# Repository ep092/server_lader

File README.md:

# server_lader

## Umbau eines ESP120 zu einem Ladegerät

### Trivia:
Das ESP120 ist ein 3kW starkes Servernetzteil mit einer Ausgangsspannung von standardmäßig 52V und bis zu >50A. Das Netzteil lässt sich allerdings leicht auf andere Spannungen umrüsten, um z.B. als Akkulader oder sehr potentes Labornetzteil eingesetzt zu werden.

### Was tut dieses Projekt?
dieses Projekt soll die zur Spannungsverstellung nötige Hilfsspannung aus den vom Netzteil zusätzlich bereitgestellten 5V erzeugen, die Ausgangsspannung regeln und für einen Ladestrom nach einem Ladeprogramm, das extern eingespeist wird, einstellen. Das Netzteil muss nur minimal gemoddet werden.

### Der Mod:
siehe elweb, eigene Bilder liegen im Unterordner "Bilder".
Einfach gesagt, werden an den beiden Pads des Potis "RV..." Kabel angelötet, die dann mit der Steuerplatine verbunden werden. Hier wird die Sollwertspannung eingespeist.

Es existieren Messwerte für 3 Sollwertspannungen:

* 61V 35,4 kOhm (-1,5V am Poti)
* 60V 42,5 kOhm (-1,3V am Poti)
* 59V 51,6 kOhm (-1,1V am Poti)

## Umbau auf eine andere Spannung für die Überspannungsabschaltung
Das Netzteil besitzt zusätzlich zur Regelspannung, die am Poti zu verändern ist, eine feste Spannung, bei der eine Überspannungsabschaltung stattfindet. Die soll das Netzteil und die angeschlossenen Verbraucher schützen. Teilweise ist es jedoch nötig, nahe an 60V zu kommen, beispielsweise, wenn man einen 48V-Bleiakkupack laden will. Daher ist in diesen Fällen die Überspannungsabschaltung auf einen leicht höheren Spannungswert zu verschieben. 

Dazu ist es notwendig einen zusätzlichen Widerstand parallel zu den bereits vorhandenen auf einer der Platinen einzulöten. Es handelt sich um einen SMD-Widerstand in Bauform 0805 mit dem Wert "473" also 47 kOhm, der direkt neben einem SMD-Bauteil im Gehäuse SOT-223-3 liegt. Im Ordner "Bilder" ist die Stelle zu sehen, wo der Widerstand eingelötet werden muss.

Wenn man über die bereits verbauten Widerstände im eingebauten Zustand misst, kommt man auf 4,096 Ohm. Mit einem parallel geschaltenen 51,6 kOhm Widerstand kommt man so auf einen Widerstand von 3,79kOhm

Es wird hier allerdings ein Widerstand mit 47 kOhm empfohlen, da mit diesem 60V gerade so erreicht werden, aber die Kondensatoren des Netzteils noch nicht beschädigt werden. Diese halten 63V aus. Für noch höhere Ausgangsspannungen müssten die Kondensatoren durch andere Typen mit 80V Festigkeit getauscht werden. Zusätzlich wird das Netzteil ab ca 61-62V instabil.

## Änderungen für Hardwareversion 2:
 
* Footprint für Stecker anpassen
* zusätzlicher Kondensator für AREF
* Micromatch-Stecker auf Display Platine auf Unterseite verlegen
* zweiter Stecker für I2C, um das OLED anzuschließen (JST XH, stehend)

## TODOs Software:

* I2C-Auswertung von Lüfter und Temperaturen
* Umbau auf so ein kleines OLED-Display z.b. mit der U8g-Lib

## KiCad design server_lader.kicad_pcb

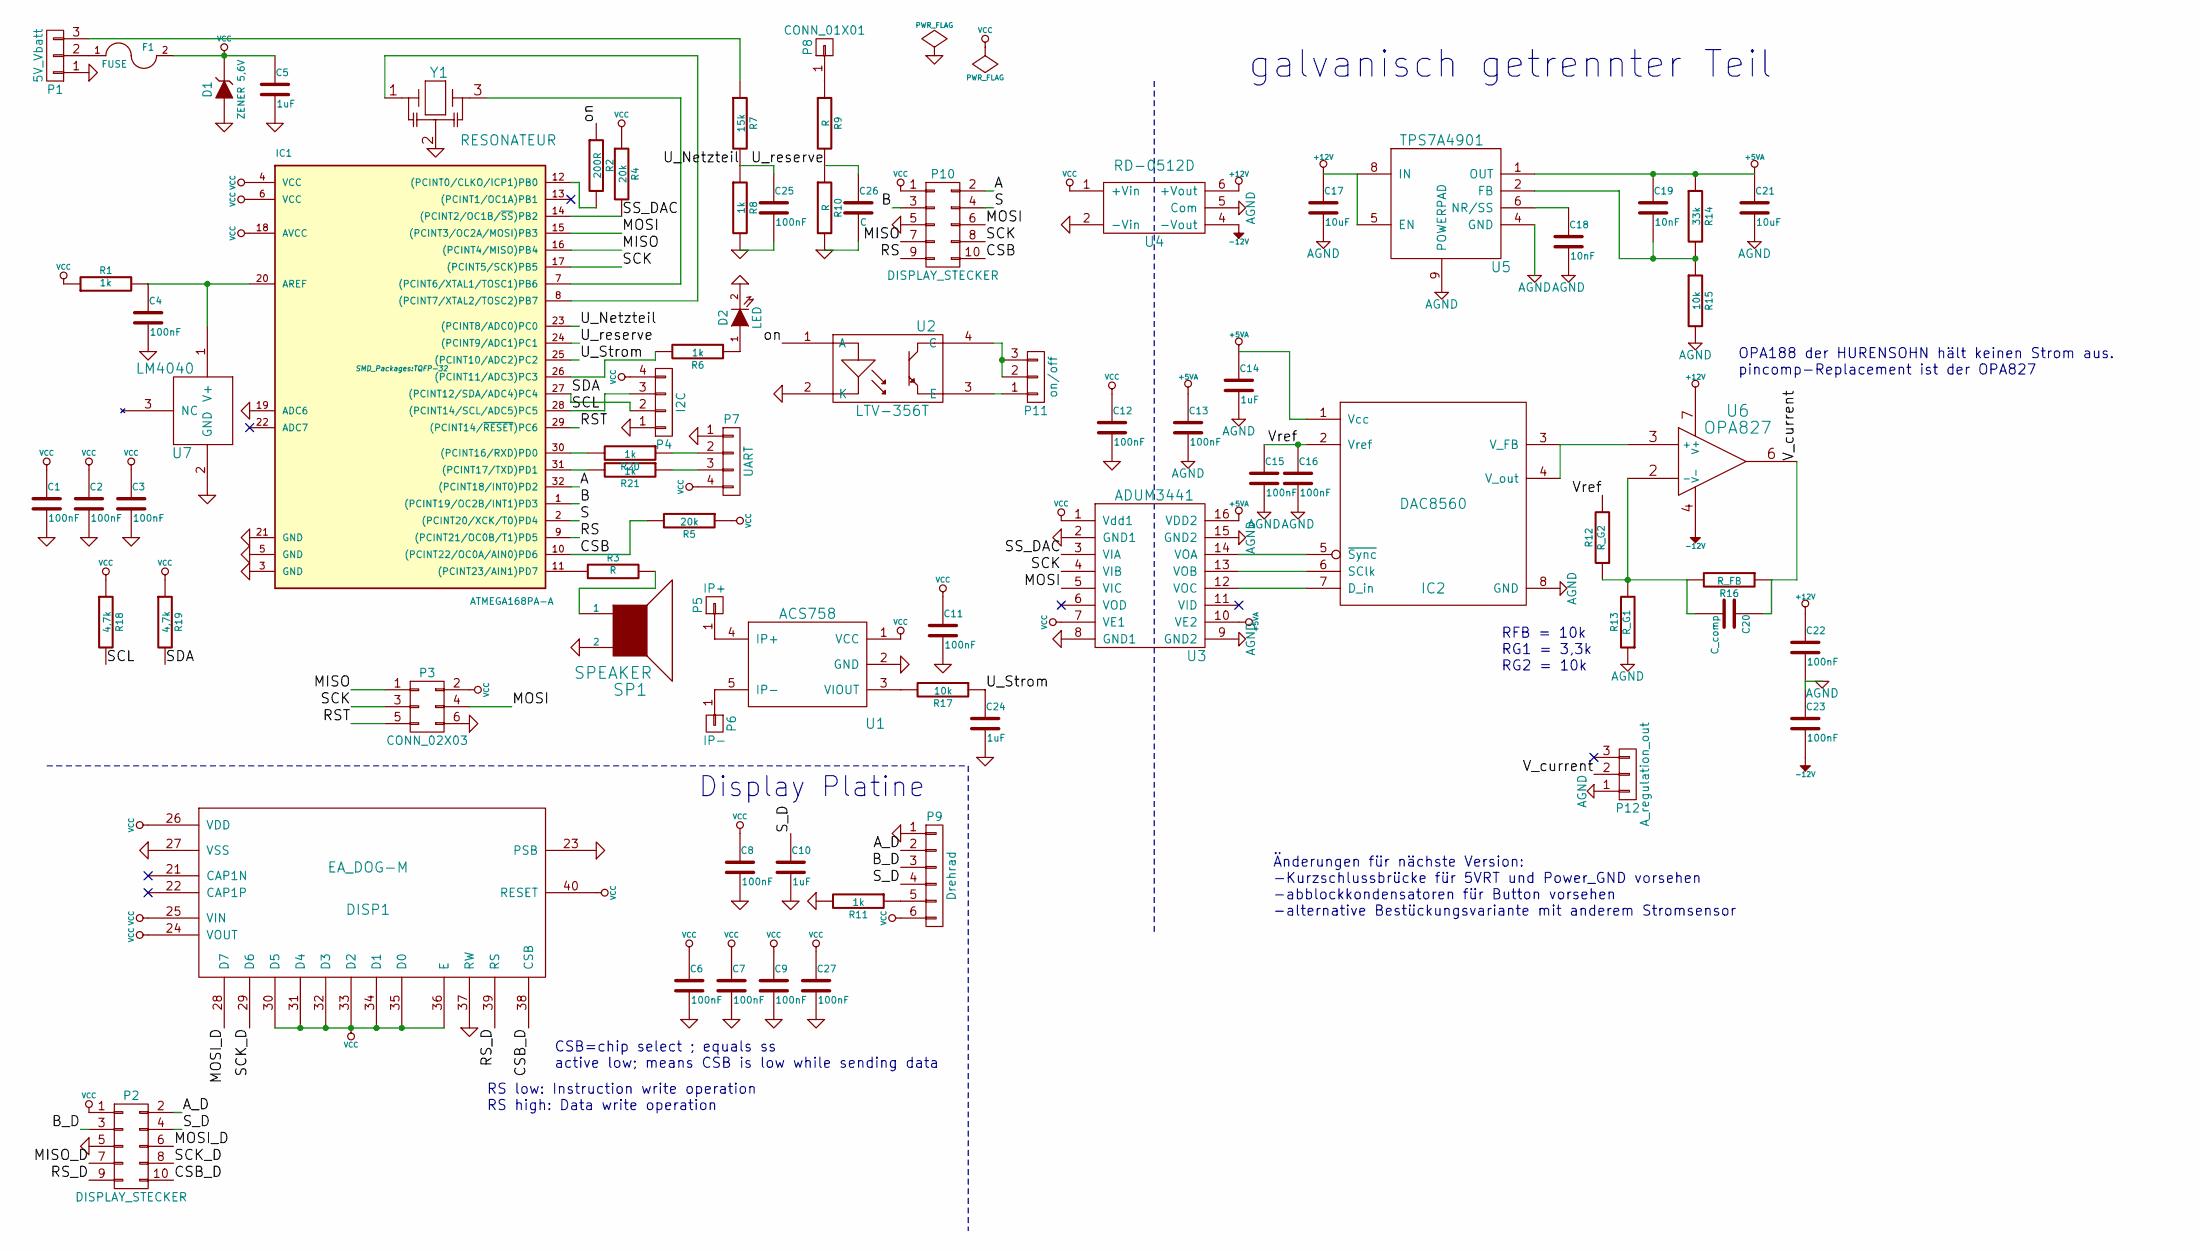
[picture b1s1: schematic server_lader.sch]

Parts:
C1, C2, C3, C4, C6, C7, C8, C9, C11, C12, C13, C15, C16, C22, C23, C27: 100nF; SMD-0402
C5, C10, C14, C24: 1uF; SMD-0603
C17, C21: 10uF; SMD-1206
C18, C19: 10nF; SMD-0402
C20: C_comp; SMD-0603
C25: 100nF; SMD-0603
C26: C; SMD-0603
D1: ZENER 5,6V; Diode-Universal-SMA-SMB_Handsoldering
D2: LED; SMD-0603
DISP1: EA_DOG-M; EA_DOG-M_DISP
F1: FUSE; fuse_holder_Schurther
IC1: ATMEGA168PA-A; TQFP-32
IC2: DAC8560; MSOP-8_3x3mm_Pitch0.65mm
P1: 5V_Vbatt; Socket_MOLEX-KK-RM2-54mm_Lock_3pin_straight
P2, P10: DISPLAY_STECKER; micro_match5x2
P3: CONN_02X03; micro_match3x2
P4: I2C; Socket_MOLEX-KK-RM2-54mm_Lock_4pin_straight
P5: IP+; power_terminal
P6: IP-; power_terminal
P7: UART; Socket_MOLEX-KK-RM2-54mm_Lock_4pin_straight
P8: CONN_01X01; SIL-1
P9: Drehrad; Socket_MOLEX-KK-RM2-54mm_Lock_6pin_straight
P11: on/off; Socket_MOLEX-KK-RM2-54mm_Lock_3pin_straight
P12: A_regulation_out; Socket_MOLEX-KK-RM2-54mm_Lock_3pin_straight
R1, R6, R8, R11, R20, R21: 1k; SMD-0805
R2: 200R; SMD-0805
R3, R9, R10: R; SMD-0805
R4, R5: 20k; SMD-0805
R7: 15k; SMD-0805
R12: R_G2; SMD-0805
R13: R_G1; SMD-0805
R14: 33k; SMD-0805
R15, R17: 10k; SMD-0805
R16: R_FB; SMD-0805
R18, R19: 4,7k; SMD-0805
SP1: SPEAKER; Buzzer_AI-1027-TWT-5V-R
U1: ACS758; ACS758_PFF
U2: LTV-356T; SO-4
U3: ADUM3441; SOIC-16_7.5x10.3mm_Pitch1.27mm
U4: RD-0512D; RD-xx12D
U5: TPS7A4901; MSOP-8_power_pad
U6: OPA827; SSOP-8
U7: LM4040; SOT-23
Y1: RESONATEUR; CerOsc_3,2x1,3

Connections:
+5VA: C13.1, C14.1, C19.1, C21.1, IC2.1 (Vcc), R14.1, U3.10 (VE2), U3.16 (VDD2), U5.1 (OUT)
+12V: C17.1, C22.1, U4.6 (+Vout), U5.5 (EN), U5.8 (IN), U6.7 (V+)
-12V: C23.2, U4.4 (-Vout), U6.4 (V-)
/A: IC1.32 ((PCINT18/INT0)PD2), P10.2
/A_D: P2.2, P9.2
/B: IC1.1 ((PCINT19/OC2B/INT1)PD3), P10.3
/B_D: P2.3, P9.3
/CSB: IC1.10 ((PCINT22/OC0A/AIN0)PD6), P10.10, R5.2
/CSB_D: DISP1.38 (CSB), P2.10
/MISO: IC1.16 ((PCINT4/MISO)PB4), P3.1, P10.7
/MOSI: IC1.15 ((PCINT3/OC2A/MOSI)PB3), P3.4, P10.6, U3.5 (VIC)
/MOSI_D: DISP1.28 (D7), P2.6
/RS: IC1.9 ((PCINT21/OC0B/T1)PD5), P10.9
/RST: IC1.29 ((PCINT14/~RESET~)PC6), P3.5
/RS_D: DISP1.39 (RS), P2.9
/S: IC1.2 ((PCINT20/XCK/T0)PD4), P10.4
/SCK: IC1.17 ((PCINT5/SCK)PB5), P3.3, P10.8, U3.4 (VIB)
/SCK_D: DISP1.29 (D6), P2.8
/SCL: IC1.28 ((PCINT14/SCL/ADC5)PC5), P4.3, R18.2
/SDA: IC1.27 ((PCINT12/SDA/ADC4)PC4), P4.2, R19.2
/SS_DAC: IC1.14 ((PCINT2/OC1B/~SS~)PB2), R4.2, U3.3 (VIA)
/S_D: C10.1, P2.4, P9.4
/U_Netzteil: C25.1, IC1.23 ((PCINT8/ADC0)PC0), R7.2, R8.1
/U_Strom: C24.1, IC1.25 ((PCINT10/ADC2)PC2), R17.1
/U_reserve: C26.1, IC1.24 ((PCINT9/ADC1)PC1), R9.2, R10.1
/V_current: C20.1, P12.2, R16.1, U6.6
/Vref: C15.1, C16.1, IC2.2 (Vref), R12.2
/on: R2.1, U2.1 (A)
AGND: C13.2, C14.2, C15.2, C16.2, C17.2, C18.2, C21.2, C22.2, C23.1, IC2.8 (GND), P12.1, R13.1, R15.2, U3.9 (GND2), U3.15 (GND2), U4.5 (Com), U5.4 (GND), U5.9 (POWERPAD)
GND: C1.2, C2.2, C3.2, C4.2, C5.2, C6.2, C7.2, C8.2, C9.2, C10.2, C11.2, C12.2, C24.2, C25.2, C26.2, C27.2, D1.1 (A), D2.2 (K), DISP1.23 (PSB), DISP1.27 (VSS), DISP1.37 (RW), IC1.3 (GND), IC1.5 (GND), IC1.19 (ADC6), IC1.21 (GND), P1.1, P2.5, P3.6, P4.1, P7.1, P9.1, P10.5, R8.2, R10.2, R11.2, SP1.2, U1.2 (GND), U2.2 (K), U3.2 (GND1), U3.8 (GND1), U4.2 (-Vin), U7.2 (GND), Y1.2
unnamed: C4.1, IC1.20 (AREF), R1.2, U7.1 (V+)
unnamed: C18.1, U5.6 (NR/SS)
unnamed: C19.2, R14.2, R15.1, U5.2 (FB)
unnamed: C20.2, R12.1, R13.2, R16.2, U6.2 (-)
unnamed: D2.1 (A), R6.1
unnamed: F1.1, P1.2
unnamed: IC1.7 ((PCINT6/XTAL1/TOSC1)PB6), Y1.3
unnamed: IC1.8 ((PCINT7/XTAL2/TOSC2)PB7), Y1.1
unnamed: IC1.11 ((PCINT23/AIN1)PD7), R3.1
unnamed: IC1.12 ((PCINT0/CLKO/ICP1)PB0), R2.2
unnamed: IC1.26 ((PCINT11/ADC3)PC3), R6.2
unnamed: IC1.30 ((PCINT16/RXD)PD0), R20.2
unnamed: IC1.31 ((PCINT17/TXD)PD1), R21.2
unnamed: IC2.3 (V_FB), IC2.4 (V_out), U6.3 (+)
unnamed: IC2.5 (~Sync), U3.14 (VOA)
unnamed: IC2.6 (SClk), U3.13 (VOB)
unnamed: IC2.7 (D_in), U3.12 (VOC)
unnamed: P1.3, R7.1
unnamed: P5.1, U1.4 (IP+)
unnamed: P6.1, U1.5 (IP-)
unnamed: P7.2, R20.1
unnamed: P7.3, R21.1
unnamed: P8.1, R9.1
unnamed: P9.5, R11.1
unnamed: P11.1, U2.3 (E)
unnamed: P11.2, P11.3, U2.4 (C)
unnamed: R3.2, SP1.1
unnamed: R17.2, U1.3 (VIOUT)
VCC: C1.1, C2.1, C3.1, C5.1, C6.1, C7.1, C8.1, C9.1, C11.1, C12.1, C27.1, D1.2 (K), DISP1.24 (VOUT), DISP1.25 (VIN), DISP1.26 (VDD), DISP1.30 (D5), DISP1.31 (D4), DISP1.32 (D3), DISP1.33 (D2), DISP1.34 (D1), DISP1.35 (D0), DISP1.36 (E), DISP1.40 (RESET), F1.2, IC1.4 (VCC), IC1.6 (VCC), IC1.18 (AVCC), P2.1, P3.2, P4.4, P7.4, P9.6, P10.1, R1.1, R4.1, R5.1, R18.1, R19.1, U1.1 (VCC), U3.1 (Vdd1), U3.7 (VE1), U4.1 (+Vin)

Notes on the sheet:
galvanisch getrennter Teil
CSB=chip select ; equals ss active low; means CSB is low while sending data
RS low: Instruction write operation RS high: Data write operation
Display Platine
RFB = 10k RG1 = 3,3k RG2 = 10k
Änderungen für nächste Version: -Kurzschlussbrücke für 5VRT und Power_GND vorsehen -abblockkondensatoren für Button vorsehen -alternative Bestückungsvariante mit anderem Stromsensor
OPA188 der HURENSOHN hält keinen Strom aus. pincomp-Replacement ist der OPA827

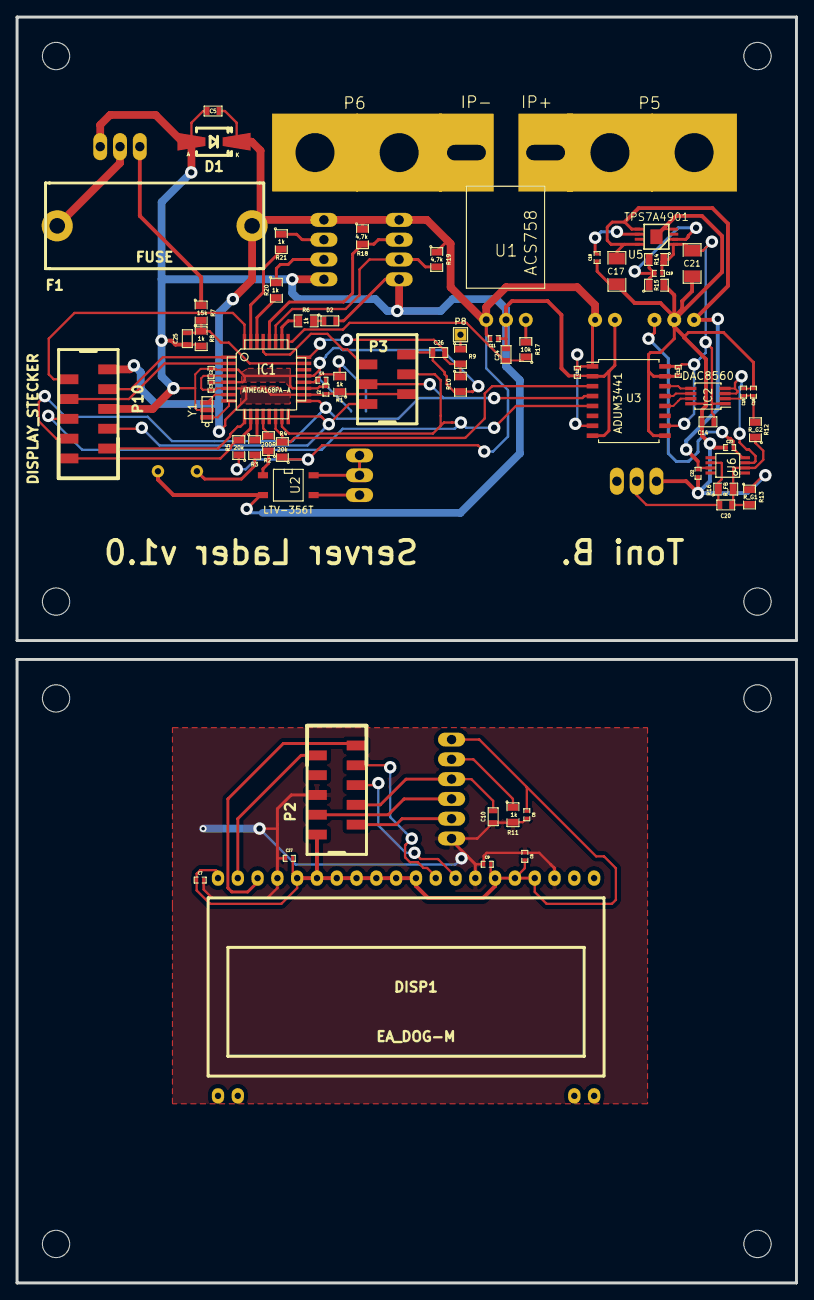
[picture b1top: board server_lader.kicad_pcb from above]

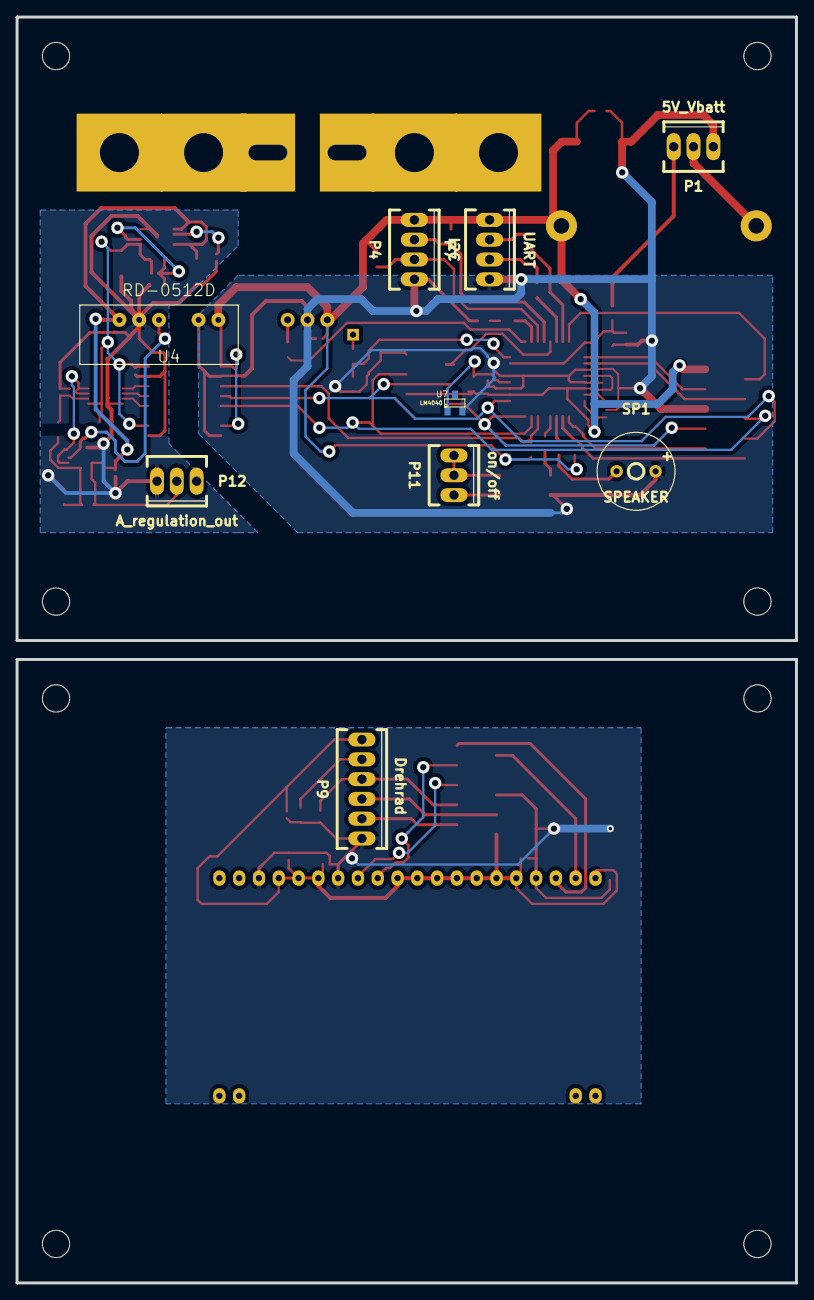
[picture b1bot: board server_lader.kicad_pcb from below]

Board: 2 copper layers, 100.0 x 162.4 mm, 77 parts (9 on the bottom side), 59 nets.

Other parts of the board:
Outl: EuroBoard_halb_Type-I_100mmX80mm_holes
Outl#2: EuroBoard_halb_Type-I_100mmX80mm_holes

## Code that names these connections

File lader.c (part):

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#define I2C_DDR DDRC
#define I2C_PORT PORTC
#define I2C_PIN PINC
#define SCL PC5
#define SDA PC4
uint8_t ERR = 0;
#include "../AtmelLib/io/serial/i2c.h"

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#ifndef OLED
#define DISPLAY_RS_DDR   DDRD
#define DISPLAY_RS_PORT	 PORTD
#define DISPLAY_RS_PIN	 PD5
#define DISPLAY_CSB_DDR  DDRD
#define DISPLAY_CSB_PORT PORTD
#define DISPLAY_CSB_PIN  PD6
#include "EA_DOGM163L-A-Atmel-Lib/EA_DOGM163L-A.c"
#endif

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// OLED-Lib einbinden
#endif

#define LED(x) out(PORTC,PC3,0,x)
// #define NT_ON(x) out(PORTB,PB0,0,x)
#define SPKR(x) out(PORTD,PD7,0,x)
#define SS_DAC(x) out(PORTB,PB2,0,x)

#define B_KNOPF_LOSGELASSEN (knopf & 1) 
#define RESET_KNOPF_LOSGELASSEN cbi(knopf, 0) 
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}

void ntOn(uint8_t ausgang) {
	// (PORTB,PB0,0,x)
	if (ausgang == 0) {
		cbi(PORTB, PB0);
		wdt_disable();
	} else {
		wdt_enable(WDTO_500MS);
		sbi(PORTB, PB0);
	}
}

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
// KNOPFDRUCK oder loslassen
ISR (PCINT2_vect, ISR_BLOCK) {
	if(PIND & 1<<PD4) { // Knopf ist gerade losgelassen worden
		sbi(knopf, 0);
		cbi(knopf, 1); // lösche gedrückt-Bit wieder
	} else { // Knopf gedrückt, warte auf loslassen
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}

int main(void) {
	DDRB  = 1<<PB0 | 1<<PB2 | 1<<PB3 | 1<<PB5;
	DDRC  = 1<<PC3 | 1<<PC5;
	DDRD  = 1<<PD1 | 1<<PD5 | 1<<PD6 | 1<<PD7;
	// Pullups
	PORTD = 1<<PD4;
	
	// Sicherer Start nach Boot des Geräts:
	ntOn(0);
	
	// Pinchange Interrupts für das Drehrad und den Knopf
	// Knopf hängt am PCINT20 (PD4)
	EICRA = 1<<ISC11 | 1<<ISC10 | 1<<ISC01 | 1<<ISC00;
	EIMSK = 1<<INT1 | 1<<INT0;
	PCICR = 1<<PCIE2; // PCINT16 bis 23 aktiv
	PCMSK2 = 1<<PCINT20; // Interrupt auf fallender UND steigender Flanke von PD4
	
	delayms(100); // wait for clock stabilize
	
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
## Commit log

2014-11-09 init
2014-11-11 1st commit from VT7, lib für den DAC erstellt und readme weitergeschrieben.
2014-11-11 datenblätter für DAC und spannungswandler
2014-11-11 datenblatt vom Recom-Spannungswandler dazugefügt
2014-11-11 work
2014-11-11 bugfixes
2014-11-12 Bilder vom Netzteil hinzugefügt.
2014-11-12 Update README.md
    Umbau auf 60V
2014-11-13 app note von TI hinzugefügt
2014-11-13 work Datenblatt hinzugefügt
2014-11-15 layout fertig
2014-11-15 ps files added
2014-11-15 gitignore dazugefügt, dass das chaos mal ein ende nimmt.
2014-11-15 pr0grammdateien mal dazu....
2014-11-15 submodule für die lib des LCDs erstellt.
2014-11-15 pr0gramm geht los. Gleitmittelwerte für alle ADC-Messungen um Ungenauigkeiten zu vermindern.
2014-11-16 Update README.md
    ovp Widerstände hinzugefügt
2014-11-16 DOGlib und ein paar Änderungen am lader.c
2014-11-16 repariere lib
2014-11-16 vermessung der Regelspannung im Verhältnis zur Ausgangsspannung
2014-11-16 unterordner erstellt
2014-11-16 pr0gramm geht weiter. Viele Interrupts bestimmen den Programmablauf!
2014-11-16 drehdruck-Knopf auslesung geschrieben
2014-11-16 Berechnung für die DAC-Stellwerte in Abhängigkeit von der gewünschten Ausgangsspannung
2014-11-16 fehler entfernt
2014-11-16 kleine Änderungen
2014-11-16 ein paar Bilderlein zum MOD der OVLO.
2014-11-16 fehleränderung im Bild
2014-11-17 datenblatt vom HP-Netzteil ESP120 dazugefügt
2014-11-17 footprint of fuseholder changed
2014-11-17 ADC änderungen
2014-11-18 anfang der menüstruktur und der Regelung
2014-11-18 Programmablaufdiagramm erstellt. jedenfalls teilweise.
2014-11-23 für Fertigung vorbereitet
2014-11-28 neue Dateien - Version so gefertigt.
2014-11-28 programm tut noch nicht vollständig, Timer und ADC laufen.
2014-11-29 flowchart.c hinzugefügt
2014-11-29 compiles without errors but still a lot of work to do
2014-11-29 Menü Grundfunktionen laufen
2014-11-29 menü läuft spannungseinstellung läuft
2014-11-30 stromeinstellung hinzugefügt
2014-11-30 bugfix
2014-11-30 bugfixes und Vormerkungen für nächsten Version
2014-11-30 bereits in lader.c integriert
2014-12-01 neue Bilder und Regelung für den Netzteilmodus
2014-12-01 Datenblätter und Schaltplananpassungen wegen neuem OPV im Ausgangszweig
2014-12-02 unterstützung für PSTR dazu
2014-12-02 Fehlercodes und deren Verarbeitung dazu, Modus Netzteil
2014-12-02 Laderegelung sollte fertig sein, Netzteil auch. UART spuckt schon ein paar Daten aus, Energiemessung noch NICHT fertig.
2014-12-03 bugfixes Stromanzeige ist fehlerhaft
2014-12-03 fertig zum testen TODO: beim lesen der variablen strom interrupts sperren
2014-12-04 Umlaute werden korrekt angezeigt
2014-12-05 netzteilfunktion getestet
2014-12-05 regelung schneller gemacht
2014-12-05 lader sollte gehen... tut er aber nicht
2014-12-05 interruptsicherheit in netzteil und lader erhöht
2014-12-06 lader geht jetzt *wirklich*, Netzteil sowieso.
2014-12-07 bugfixes version testing
2014-12-30 Diagramm, wie das Netzteil mit dem ServerLader verbunden werden soll.
2014-12-30 Bilder von einem Aufbau des Laders mit industriell gefertigter Platine, allerdings noch ohne Display
2014-12-31 weitere änderungen für fernsteuerung- noch nicht in Funktion.
2015-01-01 konsole geht fürs laden - RL test steht noch aus.
2015-01-01 Datenblatt vom i2c Protokoll dazugefügt und fernsteuerung für lader so weit fertig, dass es getestet werden kann (WiP)
2015-02-03 fernsteuerung jetzt auch für den Lademodus - allerdings noch etwas buggy
2015-02-18 fersteuerung weiter - aufhängung noch nicht behoben!
2015-03-06 Fernsteuercode neu geschrieben und stark vereinfacht. Aufhänger nicht mehr reproduzierbar.
2015-03-07 watchdog integriert und Fernsteuerung weiter
2015-03-07 Lademodus kann nun auch remote abgebrochen werden!
2015-03-09 Regelung im Netzteilmodus konnte springen - behoben
2015-03-09 Netzteil: Überspannungsschwellwert auf 1,5V gestellt und RampUp-Behandlung mit einem eigenen Errorstate verbaut. bei Reglerwert > 3V gibt es einen Fehler.
2015-03-09 Stromkalibrierung repariert.
2015-06-25 stromkalibrierung beim Lader verbessert - test steht aus
2015-11-15 logo hinzugefügt
2015-12-27 Taster entprellung verbessert
2015-12-29 Anzeigefehler bei der Stromeinstellung behoben
2016-06-26 Layout verbessert und weitere Hinweise zum Modding geschrieben
2016-06-26 Datenblätter umbenannt, dass man auch was versteht.
2016-06-26 rescue_lib für schaltplan angelegt

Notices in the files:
lader.c:
License: GPLv3 or later
Author: Copyright (C) Philipp Hörauf, Toni
This program is free software; you can redistribute it and/or modify
it under the terms of the GNU General Public License as published by
the Free Software Foundation; either version 2 of the License, or
(at your option) any later version.
